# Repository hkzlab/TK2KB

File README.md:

# TK2KB

## DISCLAIMER

Any use of this project is **under your own responsibility**.
You will be responsible of checking the correct construction and functionality of your board.
By using this project You will agree that I cannot be held responsible if it will destroy any of your devices, damage your computer, burn down your house or whatever.

## Introduction

I recently built for myself a [TK2000 clone](https://github.com/clemarfolly/Microdigital-TK2000), but I don't have a keyboard to use it so,
before making an expensive mechanical one, I decided to test the design making one with some cheap SMD switches I had around.

## Hardware

The board was designed with [KiCad](https://kicad.org/) EDA.

### Bill of Materials

| Component              | Qty | Type / Value                                            | Notes                                                                |
| ---------------------- | --- | ------------------------------------------------------- | -------------------------------------------------------------------- |
| D1                     |  1  | 3mm THT LED                                             | Optional                                                             |
| J1                     |  1  | 1x08 2.54mm, right angle pinheader                      |                                                                      |
| J2                     |  1  | 1x13 2.54mm, right angle pinheader                      |                                                                      |
| J3                     |  1  | 1x02 2.54mm, right angle pinheader                      | Optional                                                             |
| SW1-SW57               |  57 | SMD push buttons                                        | KSC241G or compatible                                                |

### Ordering the boards

You can order the board for this project at [PCBWay](https://www.pcbway.com/project/shareproject/TK2KB_TK2000_Keyboard_0d20454f.html) and support me or download 
the gerbers and have them printed wherever you like!!!

### 💰 Selling these boards 💰

I you want to contact me about selling this project, you can reach me via email at `0hkzUNDERSCOREprojects6ATposteoDOTnet` after properly fixing the email address by removing the digits and replacing the uppercase words with the proper characters.

**Contacts via other channels will be ignored**, as it means you did not read this document thoroughly.

"Collaborations" will boil down to the following:

- If you wish to produce and share this project at a loss or at cost, go for it. I am only asking for attribution and to let me know via email.
- If you want to do it for profit, let's discuss it. I'll probably settle for a rough 5% of the profit. Importing components is getting more expensive by the day, so this will contribute to me making future projects available for free.
- I will NOT do customer assistance for you or your customers. This is a hobby, not my job.

If this is not ok for you, you're cordially invited to go bother someone else :)

Authorized sellers will be listed in this README. If you find someone selling my boards without being listed here, it means they're stealing other people's work.

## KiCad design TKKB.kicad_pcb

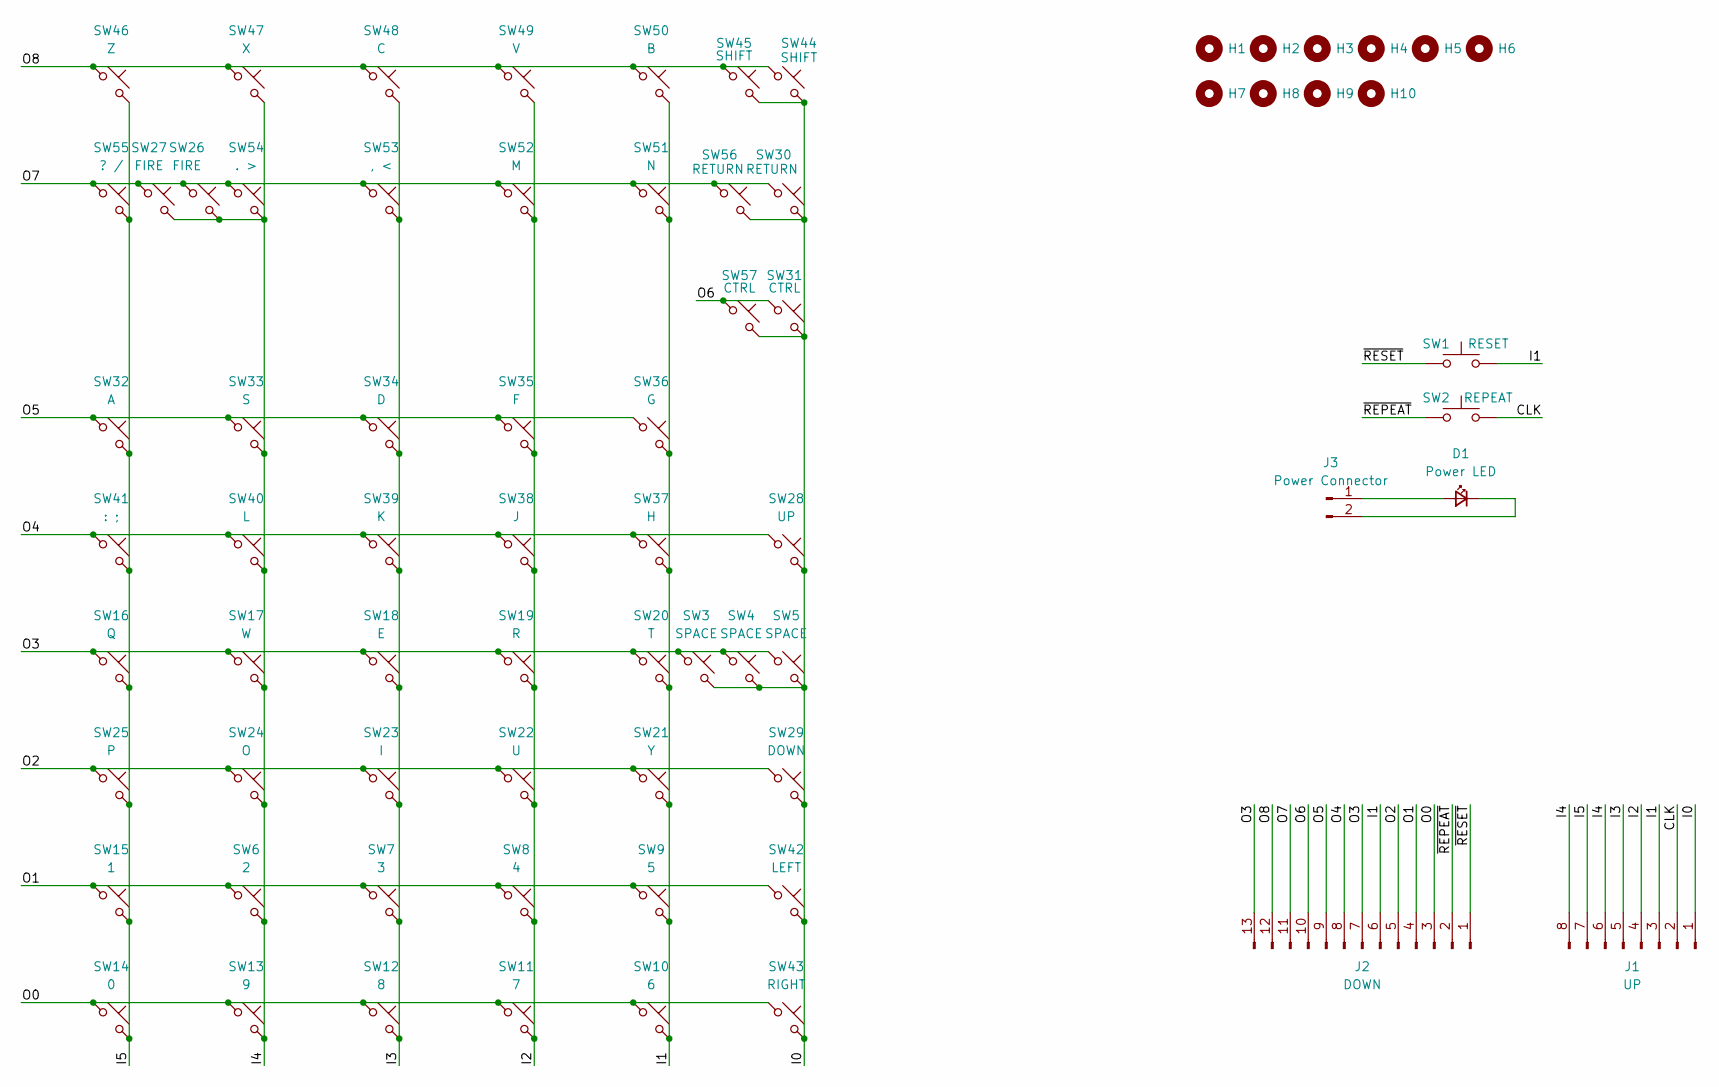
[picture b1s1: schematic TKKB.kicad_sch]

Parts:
D1: Power LED; LED_D3.0mm
H1, H2, H3, H4, H5, H6, H7, H8, H9, H10: MountingHole_Pad; MountingHole_3.2mm_M3_ISO7380
J1: UP; PinHeader_1x08_P2.54mm_Vertical
J2: DOWN; PinHeader_1x13_P2.54mm_Vertical
J3: Power Connector; PinHeader_1x02_P2.54mm_Vertical
SW1: RESET; SW_Push_SMD_Large
SW2: REPEAT; SW_Push_SMD_Large
SW3, SW4, SW5: SPACE; SW_Push_SMD_Large
SW6: 2; SW_Push_SMD_Large
SW7: 3; SW_Push_SMD_Large
SW8: 4; SW_Push_SMD_Large
SW9: 5; SW_Push_SMD_Large
SW10: 6; SW_Push_SMD_Large
SW11: 7; SW_Push_SMD_Large
SW12: 8; SW_Push_SMD_Large
SW13: 9; SW_Push_SMD_Large
SW14: 0; SW_Push_SMD_Large
SW15: 1; SW_Push_SMD_Large
SW16: Q; SW_Push_SMD_Large
SW17: W; SW_Push_SMD_Large
SW18: E; SW_Push_SMD_Large
SW19: R; SW_Push_SMD_Large
SW20: T; SW_Push_SMD_Large
SW21: Y; SW_Push_SMD_Large
SW22: U; SW_Push_SMD_Large
SW23: I; SW_Push_SMD_Large
SW24: O; SW_Push_SMD_Large
SW25: P; SW_Push_SMD_Large
SW26, SW27: FIRE; SW_Push_SMD_Large
SW28: UP; SW_Push_SMD_Large
SW29: DOWN; SW_Push_SMD_Large
SW30, SW56: RETURN; SW_Push_SMD_Large
SW31, SW57: CTRL; SW_Push_SMD_Large
SW32: A; SW_Push_SMD_Large
SW33: S; SW_Push_SMD_Large
SW34: D; SW_Push_SMD_Large
SW35: F; SW_Push_SMD_Large
SW36: G; SW_Push_SMD_Large
SW37: H; SW_Push_SMD_Large
SW38: J; SW_Push_SMD_Large
SW39: K; SW_Push_SMD_Large
SW40: L; SW_Push_SMD_Large
SW41: : ;; SW_Push_SMD_Large
SW42: LEFT; SW_Push_SMD_Large
SW43: RIGHT; SW_Push_SMD_Large
SW44, SW45: SHIFT; SW_Push_SMD_Large
SW46: Z; SW_Push_SMD_Large
SW47: X; SW_Push_SMD_Large
SW48: C; SW_Push_SMD_Large
SW49: V; SW_Push_SMD_Large
SW50: B; SW_Push_SMD_Large
SW51: N; SW_Push_SMD_Large
SW52: M; SW_Push_SMD_Large
SW53: , <; SW_Push_SMD_Large
SW54: . >; SW_Push_SMD_Large
SW55: ? /; SW_Push_SMD_Large

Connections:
/CLK: J1.2, SW2.2
/I0: J1.1, SW3.2, SW4.2, SW5.2, SW28.2, SW29.2, SW30.2, SW31.2, SW42.2, SW43.2, SW44.2, SW45.2, SW56.2, SW57.2
/I1: J1.3, J2.6, SW1.2, SW9.2, SW10.2, SW20.2, SW21.2, SW36.2, SW37.2, SW50.2, SW51.2
/I2: J1.4, SW8.2, SW11.2, SW19.2, SW22.2, SW35.2, SW38.2, SW49.2, SW52.2
/I3: J1.5, SW7.2, SW12.2, SW18.2, SW23.2, SW34.2, SW39.2, SW48.2, SW53.2
/I4: J1.6, J1.8, SW6.2, SW13.2, SW17.2, SW24.2, SW26.2, SW27.2, SW33.2, SW40.2, SW47.2, SW54.2
/I5: J1.7, SW14.2, SW15.2, SW16.2, SW25.2, SW32.2, SW41.2, SW46.2, SW55.2
/O0: J2.3, SW10.1, SW11.1, SW12.1, SW13.1, SW14.1, SW43.1
/O1: J2.4, SW6.1, SW7.1, SW8.1, SW9.1, SW15.1, SW42.1
/O2: J2.5, SW21.1, SW22.1, SW23.1, SW24.1, SW25.1, SW29.1
/O3: J2.7, J2.13, SW3.1, SW4.1, SW5.1, SW16.1, SW17.1, SW18.1, SW19.1, SW20.1
/O4: J2.8, SW28.1, SW37.1, SW38.1, SW39.1, SW40.1, SW41.1
/O5: J2.9, SW32.1, SW33.1, SW34.1, SW35.1, SW36.1
/O6: J2.10, SW31.1, SW57.1
/O7: J2.11, SW26.1, SW27.1, SW30.1, SW51.1, SW52.1, SW53.1, SW54.1, SW55.1, SW56.1
/O8: J2.12, SW44.1, SW45.1, SW46.1, SW47.1, SW48.1, SW49.1, SW50.1
/~REPEAT: J2.2, SW2.1
/~RESET: J2.1, SW1.1
unnamed: D1.2 (A), J3.1
unnamed: D1.1 (K), J3.2

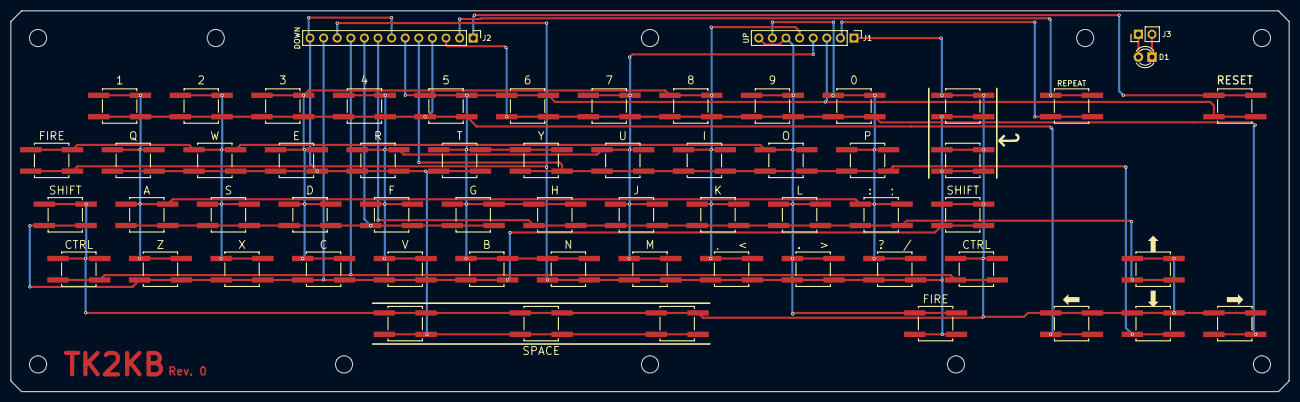
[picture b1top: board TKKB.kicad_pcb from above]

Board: 2 copper layers, 238.8 x 71.1 mm, 71 parts (0 on the bottom side), 20 nets.

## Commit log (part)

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2025-05-20 Begin working on TK2000 keyboard
2025-05-20 Add all keys to schematic
2025-05-20 Completed drawing the keyboard matrix
2025-05-20 Begin drawing PCB
2025-05-21 Created the base keyboard
2025-05-21 Update silkscreen
2025-05-21 Add measurements
2025-05-22 Add silkscreen for every key
2025-05-22 Add rev.0 gerbers
2025-05-22 Add more stand holes for the keyboard
2025-06-20 Add readme, picture and schematics
2025-06-20 Add PCBWay link
